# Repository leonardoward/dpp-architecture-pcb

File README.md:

# DPP Architecture Test Board v1.0

A single‑channel **isolated flyback power stage** on a KiCad 6 PCB, built to bench‑test
the converter used in a **Differential Power Processing (DPP)** MPPT. It is the hardware
side of the [**MultiMPPT**](https://hackaday.io/project/185092-multimppt) project &mdash; a
low‑cost, high‑efficiency MPPT with multiple independent inputs &mdash; and it implements
one converter cell from the model in
[`dpp-mppt-simulation`](https://github.com/leonardoward/dpp-mppt-simulation).

## Table of Contents

1. [What It Is](#what-it-is)
2. [How the Circuit Works](#how-the-circuit-works)
3. [Schematic](#schematic)
4. [Connectors](#connectors)
5. [Bill of Materials](#bill-of-materials)
6. [PCB](#pcb)
7. [Building the Board](#building-the-board)
8. [Repository Layout](#repository-layout)
9. [Notes & Safety](#notes--safety)
10. [License](#license)

## What It Is

In a DPP MPPT the PV modules stay in series to feed the load, and a small converter
across each module handles only the **difference** in current needed to hold that
module at its own maximum power point. This board is **one** of those converters,
broken out on its own so it can be driven, loaded and measured in isolation:

* PV / module side on `J1`, `J2`.
* String / bus side on `J4`, galvanically isolated through the transformer.
* The switching MOSFET is driven by an **external** controller (a microcontroller or a
  bench signal generator) through the 3‑pin gate‑driver header `J3` &mdash; there is no
  control loop, no sensing and no microcontroller on the board itself.

## How the Circuit Works

It is a classic isolated **flyback** converter:

1. **Input** &mdash; the module connects to `J1`/`J2`; `C1` (2200&nbsp;&micro;F) is the input
   bulk capacitor that holds the module voltage steady over a switching cycle.
2. **Switch** &mdash; `Q1` (IRFU120N N‑channel MOSFET) chops the current through the
   transformer primary. While `Q1` is on, energy is stored in the transformer core;
   when it turns off, that energy is delivered to the secondary.
3. **Gate drive** &mdash; the PWM signal enters on `J3` and is buffered by `U1`
   (DGD0215 gate driver) so the MOSFET can be switched cleanly at high frequency.
   `C2` (1&nbsp;&micro;F) decouples the driver, `R1` (1&nbsp;k) is the gate resistor and
   `R2` (100&nbsp;k) is the gate pull‑down that keeps `Q1` off when the drive is absent.
4. **Snubber / clamp** &mdash; `D1`, `D2` (1N4148W) with `C3` (47&nbsp;pF) form the
   protection network across the primary that absorbs the leakage‑inductance spike at
   turn‑off. The design allows populating either `D2 + C3` **or** `D1` alone.
5. **Transformer** &mdash; `T1` is a Würth **750311659** flyback transformer
   (180&nbsp;kHz, 1500&nbsp;Vrms primary‑to‑secondary isolation), which both transfers
   the energy and provides the galvanic isolation the DPP architecture needs.
6. **Output** &mdash; `C4` (2200&nbsp;&micro;F) filters the secondary and the converter
   output is brought out on `J4`. `R3`, `R4` are 0&nbsp;&Omega; jumpers / current‑sense
   footprints in the secondary return.

## Schematic

The full schematic is also in [`Schematic.pdf`](Schematic.pdf).

## Connectors

| Ref | Type | Purpose |
| --- | ---- | ------- |
| `J1` | Barrier terminal block | `PV+` &mdash; module positive |
| `J2` | Barrier terminal block | `PV-` &mdash; module negative |
| `J3` | 3‑pin 0.1" header | Gate drive from the external controller: `VCC`, `IN`, `GND` |
| `J4` | Barrier terminal block | `SEC` &mdash; isolated secondary / string‑bus connection |
| `H1`&ndash;`H4` | Mounting holes | &mdash; |

## Bill of Materials

| Reference | Part | Qty |
| --------- | ---- | --- |
| PCB | 2‑layer, [JLCPCB](https://jlcpcb.com/) | 1 |
| C1, C4 | 2200&nbsp;&micro;F 50&nbsp;V aluminium electrolytic, radial ([228CKS050MQW](https://www.digikey.com/en/products/detail/cornell-dubilier-illinois-capacitor/228CKS050MQW/5411846)) | 2 |
| C2 | 1&nbsp;&micro;F 25&nbsp;V X7R 0805 ([CL21B105KAFNNNE](https://www.digikey.com/en/products/detail/samsung-electro-mechanics/CL21B105KAFNNNE/3886724)) | 1 |
| C3 | 47&nbsp;pF 100&nbsp;V C0G/NP0 0805 ([08051A470JAT2A](https://www.digikey.com/en/products/detail/kyocera-avx/08051A470JAT2A/563392)) | 1 |
| D1, D2 | 100&nbsp;V 300&nbsp;mA SOD‑123 diode, 1N4148W ([1N4148W-7-F](https://www.digikey.com/en/products/detail/diodes-incorporated/1N4148W-7-F/814371)) | 2 |
| J1, J2, J4 | 9.50&nbsp;mm 2‑circuit barrier block ([OSTYK51102030](https://www.digikey.com/en/products/detail/on-shore-technology-inc/OSTYK51102030/1588818)) | 3 |
| Q1 | N‑channel 100&nbsp;V 9.4&nbsp;A IPAK / TO‑251, IRFU120N ([IRFU120NPBF](https://www.digikey.com/en/products/detail/infineon-technologies/IRFU120NPBF/812395)) | 1 |
| R1 | 1&nbsp;k&Omega; 1% 0805 ([RMCF0805FT1K00](https://www.digikey.com/en/products/detail/stackpole-electronics-inc/RMCF0805FT1K00/1760090)) | 1 |
| R2 | 100&nbsp;k&Omega; 1% 0805 ([RMCF0805FG100K](https://www.digikey.com/en/products/detail/stackpole-electronics-inc/RMCF0805FG100K/1712614)) | 1 |
| R3, R4 | 0&nbsp;&Omega; jumper 0805 ([RC0805JR-070RL](https://www.digikey.com/en/products/detail/yageo/RC0805JR-070RL/728216)) | 2 |
| T1 | Flyback transformer, 180&nbsp;kHz, 1500&nbsp;Vrms isolation, SMT ([750311659](https://www.digikey.com/en/products/detail/w%C3%BCrth-elektronik/750311659/4800066)) | 1 |
| U1 | Low‑side gate driver, inverting / non‑inverting, TSOT‑25 ([DGD0215WT-7](https://www.digikey.com/en/products/detail/diodes-incorporated/DGD0215WT-7/10130661)) | 1 |

A machine‑readable BOM is in [`dpp-architecture/dpp-architecture.csv`](dpp-architecture/dpp-architecture.csv).

## PCB

## Building the Board

* **Design files** &mdash; open `dpp-architecture/dpp-architecture.kicad_pro` in
  **KiCad 6** or newer. Project‑local symbol, footprint and 3D‑model libraries are
  under `dpp-architecture/Symbols/`, `dpp-architecture/Footprints/` and
  `dpp-architecture/3D/`.
* **Fabrication** &mdash; ready‑to‑send Gerbers and drill files are in
  `dpp-architecture/Gerber/` (and zipped as `dpp-architecture/Gerber.zip`); a step
  model of the assembly is in `dpp-architecture/Exports/`.

## Repository Layout

```
README.md                          this file
LICENSE                            GPL v3.0
Schematic.pdf                      exported schematic
Images/                            3D renders + schematic image for this README
dpp-architecture/
  dpp-architecture.kicad_pro/_sch/_pcb   KiCad 6 project
  dpp-architecture.csv               BOM
  Symbols/ Footprints/ 3D/           project-local libraries
  Gerber/  Gerber.zip                fabrication output
  Exports/                           STEP model of the board
  dpp-architecture-backups/          KiCad auto-save archive
```

## Notes & Safety

* This is a **v1.0 test fixture**, not a finished product: it exercises the power
  stage only. Closing the MPPT loop (sensing, duty‑cycle control) is done off‑board.
* The gate‑driver header exposes the drive rail; keep the external controller's ground
  common with `J3` `GND`.
* Electrolytic capacitors on both sides store charge &mdash; allow them to discharge
  before handling.
* The `dpp-architecture-backups/` folder is KiCad's auto‑save archive and is only kept
  for history; the working files are the ones directly under `dpp-architecture/`.

## License

Released under the **GNU General Public License v3.0** &mdash; see [`LICENSE`](LICENSE).

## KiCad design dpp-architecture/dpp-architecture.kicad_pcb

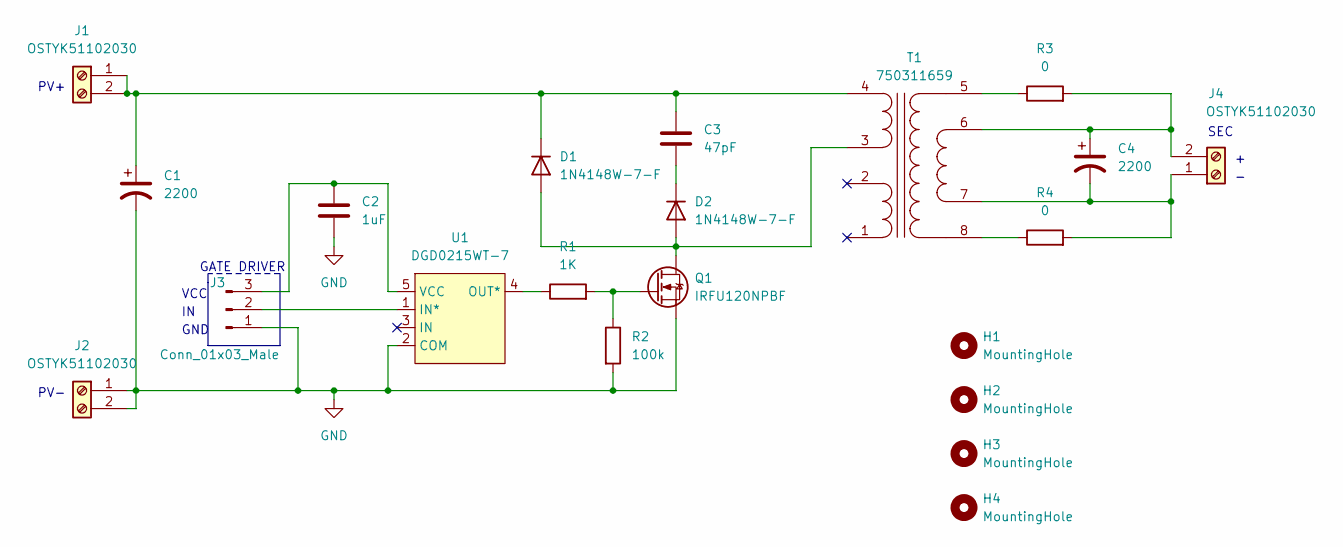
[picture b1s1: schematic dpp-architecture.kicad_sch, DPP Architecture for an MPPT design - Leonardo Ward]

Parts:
C1, C4: 2200; CP_Radial_D16.0mm_P7.50mm; Manufacturer_Part_Number 228CKS050MQW
C2: 1uF; C_0805_2012Metric; Manufacturer Part Number CL21B105KAFNNNE; LCSC C116352
C3: 47pF; C_0805_2012Metric; Manufacturer_Part_Number 08051A470JAT2A
D1, D2: 1N4148W-7-F; D_SOD-123; Manufacturer_Part_Number 1N4148W-7-F; LCSC C83528
H1, H2, H3, H4: MountingHole; MountingHole_3.5mm
J1, J2, J4: OSTYK51102030; Manufacturer_Part_Number OSTYK51102030
J3: Conn_01x03_Male; PinHeader_1x03_P2.54mm_Vertical
Q1: IRFU120NPBF; TO-251-3-1EP_Horizontal_TabDown; Manufacturer_Part_Number IRFU120NPBF; LCSC C3025
R1: 1K; R_0805_2012Metric; Manufacturer_Part_Number RMCF0805FT1K00
R2: 100k; R_0805_2012Metric_Pad1.20x1.40mm_HandSolder; Manufacturer_Part_Number RMCF0805FG100K
R3, R4: 0; R_0805_2012Metric; Manufacturer Part Number RC0805JR-070RL
T1: 750311659; Manufacturer_Part_Number 750311659
U1: DGD0215WT-7; SOT-23-5_HandSoldering; Manufacturer_Part_Number DGD0215WT-7

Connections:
GND: C1.2, C2.2, J2.1, J2.2, J3.1, Q1.3 (S), R2.2, U1.2 (COM)
unnamed: C1.1, C3.1, D1.1 (K), J1.1, J1.2, T1.4 (PRI_2)
unnamed: C2.1, J3.3, U1.5 (VCC)
unnamed: C3.2, D2.1 (K)
unnamed: C4.1, J4.2, R3.2, T1.6 (SEC_2)
unnamed: C4.2, J4.1, R4.2, T1.7 (SEC_3)
unnamed: D1.2 (A), D2.2 (A), Q1.2 (D), Q1.4 (D), T1.3 (PRI_1)
unnamed: J3.2, U1.1 (IN*)
unnamed: Q1.1 (G), R1.2, R2.1
unnamed: R1.1, U1.4 (OUT*)
unnamed: R3.1, T1.5 (SEC_1)
unnamed: R4.1, T1.8 (SEC_4)

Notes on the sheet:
VCC
SEC
PV+
GND
PV-
GATE DRIVER

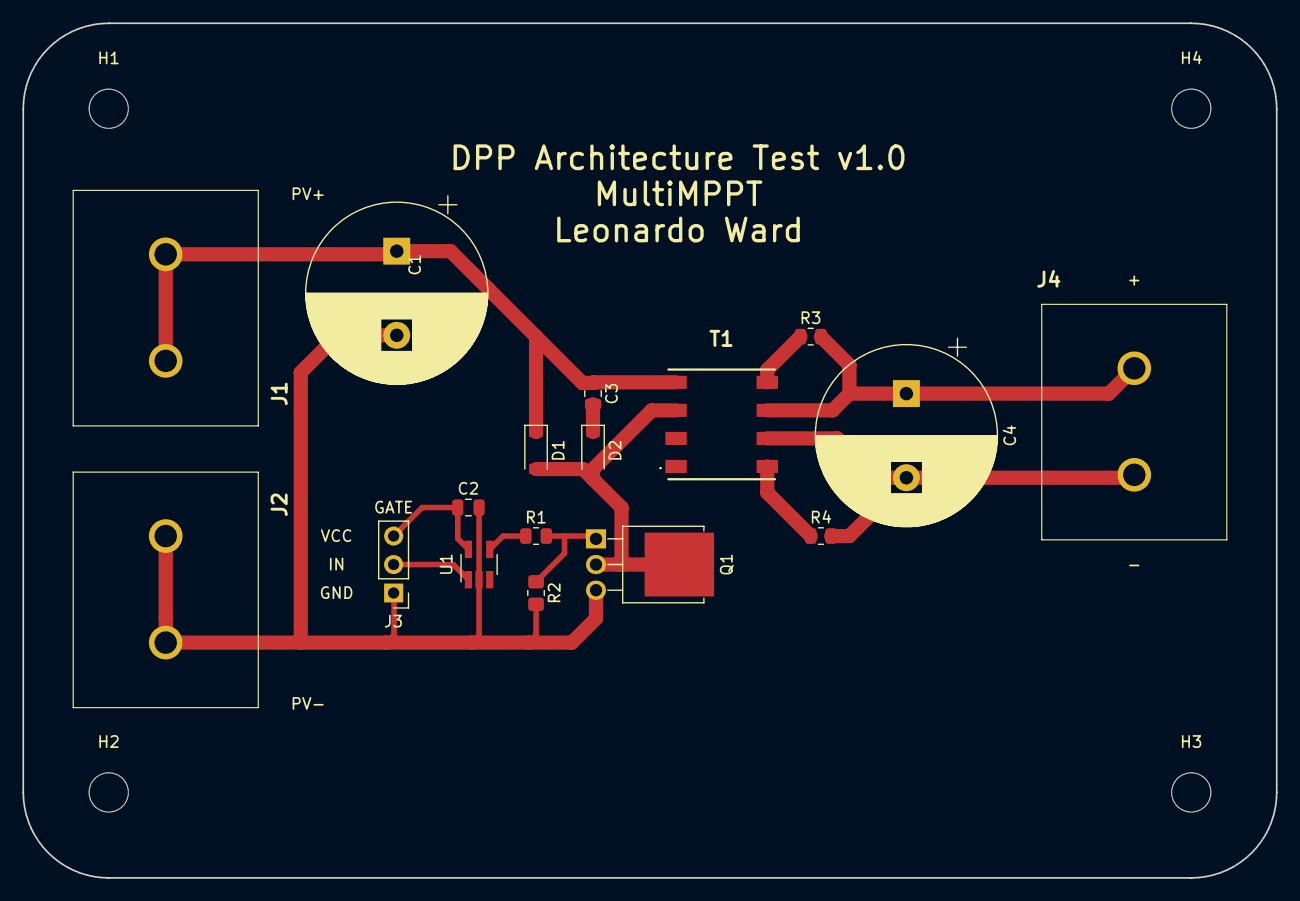
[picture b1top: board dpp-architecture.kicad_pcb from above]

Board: 2 copper layers, 111.8 x 76.2 mm, 21 parts (0 on the bottom side), 12 nets.

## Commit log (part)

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2022-04-28 Added Kicad 6 project
2022-04-29 Added kicad project, transformer and terminal blocks
2022-04-29 Added mosfet, primary and secondary capacitors and a snubber capacitor
2022-04-30 Finished schematic and pcb routing, created images of the 3D model
2022-04-30 Added 3D Model (step file)
2022-04-30 Added documentation to the readme: images of the schematic, pcb and added bill of materials
2022-04-30 Added schematic and small fixes
2022-05-01 Added 3D Models
2022-05-01 Added gerber files
